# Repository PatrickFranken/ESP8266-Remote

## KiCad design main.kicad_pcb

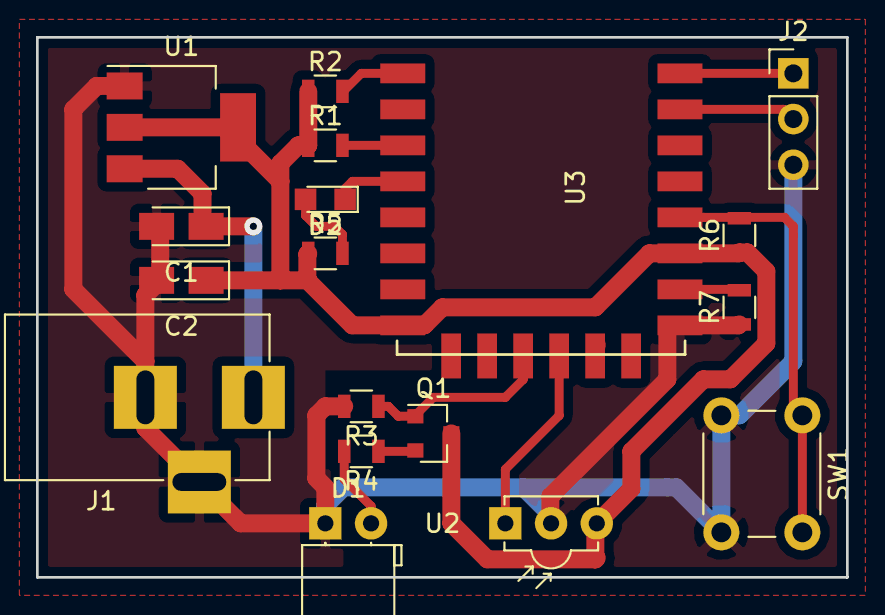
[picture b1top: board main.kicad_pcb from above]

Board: 2 copper layers, 45.0 x 30.0 mm, 18 parts (0 on the bottom side), 15 nets.

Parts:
C1, C2: 10u; CP_Tantalum_Case-A_EIA-3216-18_Reflow
D1: LED; LED_D5.0mm_Horizontal_O1.27mm_Z3.0mm
D2: LED; LED_0805
J1: BARREL_JACK
J2: CONN_01X03; Pin_Header_Straight_1x03_Pitch2.54mm
Q1: MMBT3904; SOT-23
R1, R2, R3, R6, R7: 4.7k; R_0805
R4: 39; R_0805
R5: 47; R_0805
SW1: SW_Push; SW_PUSH_6mm
U1: LM1117-3.3; SOT-223
U2: TSOP382xx; IRReceiver_Vishay_MINICAST-3pin
U3: ESP-12E; ESP-12E_SMD

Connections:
GND: C1.2, C2.2, D1.1, J1.2, J1.3, J2.3, R3.2, R7.1, SW1.2, U1.1, U2.2, U3.9
unnamed: C1.1, J1.1, U1.3
unnamed: D1.2, R4.2
unnamed: D2.1, U3.4
unnamed: D2.2, R5.2
unnamed: J2.1, U3.16
unnamed: J2.2, U3.15
unnamed: Q1.1, R3.1, U3.19
unnamed: Q1.2, R4.1
unnamed: R1.2, U3.3
unnamed: R2.2, U3.1
unnamed: R6.2, SW1.1, U3.12
unnamed: R7.2, U3.10
unnamed: U2.1, U3.20
VCC: C2.1, Q1.3, R1.1, R2.1, R5.1, R6.1, U1.2, U1.4, U2.3, U3.8, U3.11
